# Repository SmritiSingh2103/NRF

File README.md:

# NRF
nRF24L01 is a single chip radio transceiver for the world wide 2.4 - 2.5 GHz ISM
band.

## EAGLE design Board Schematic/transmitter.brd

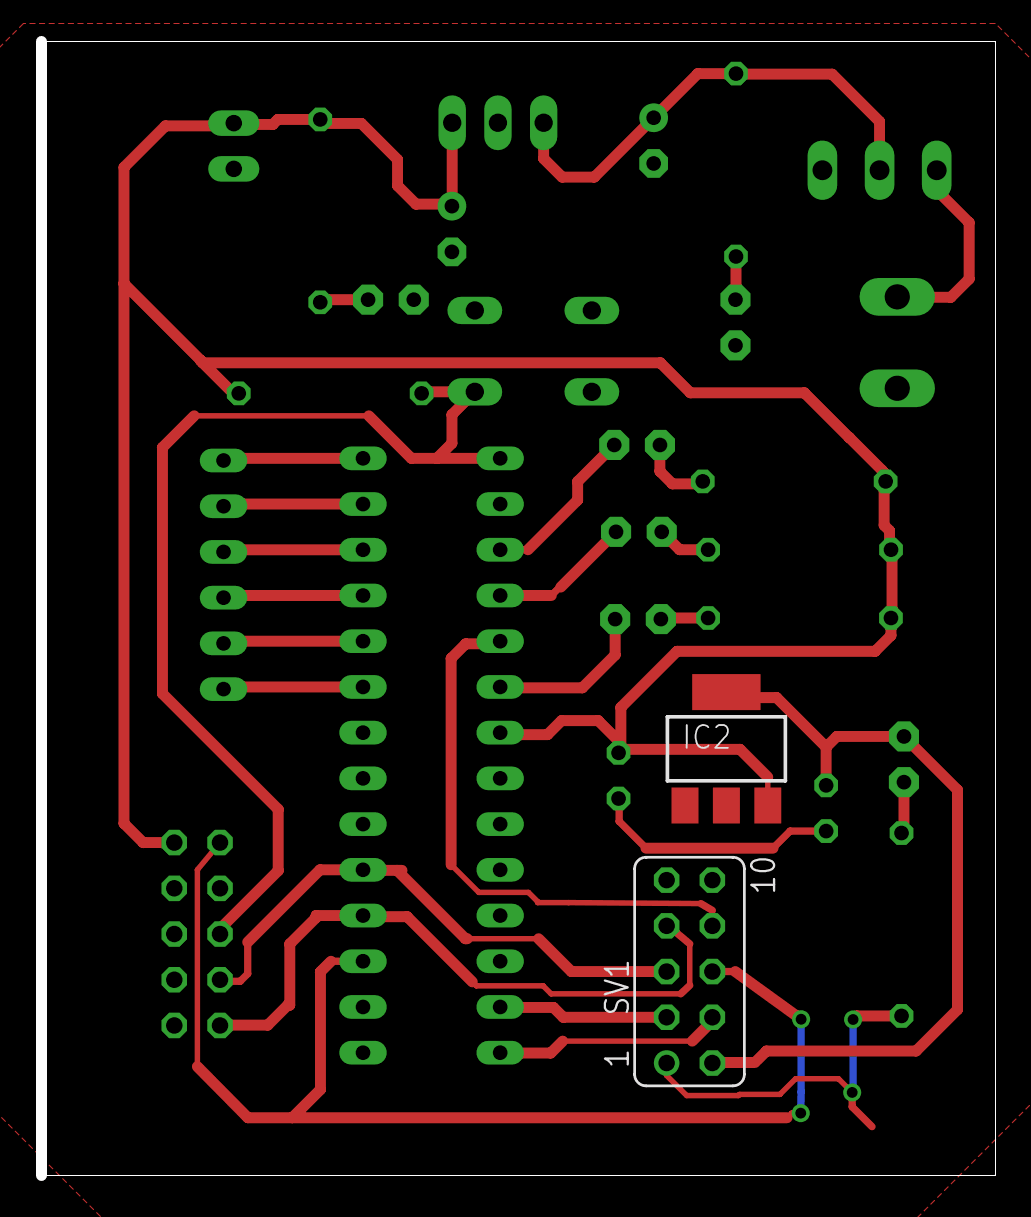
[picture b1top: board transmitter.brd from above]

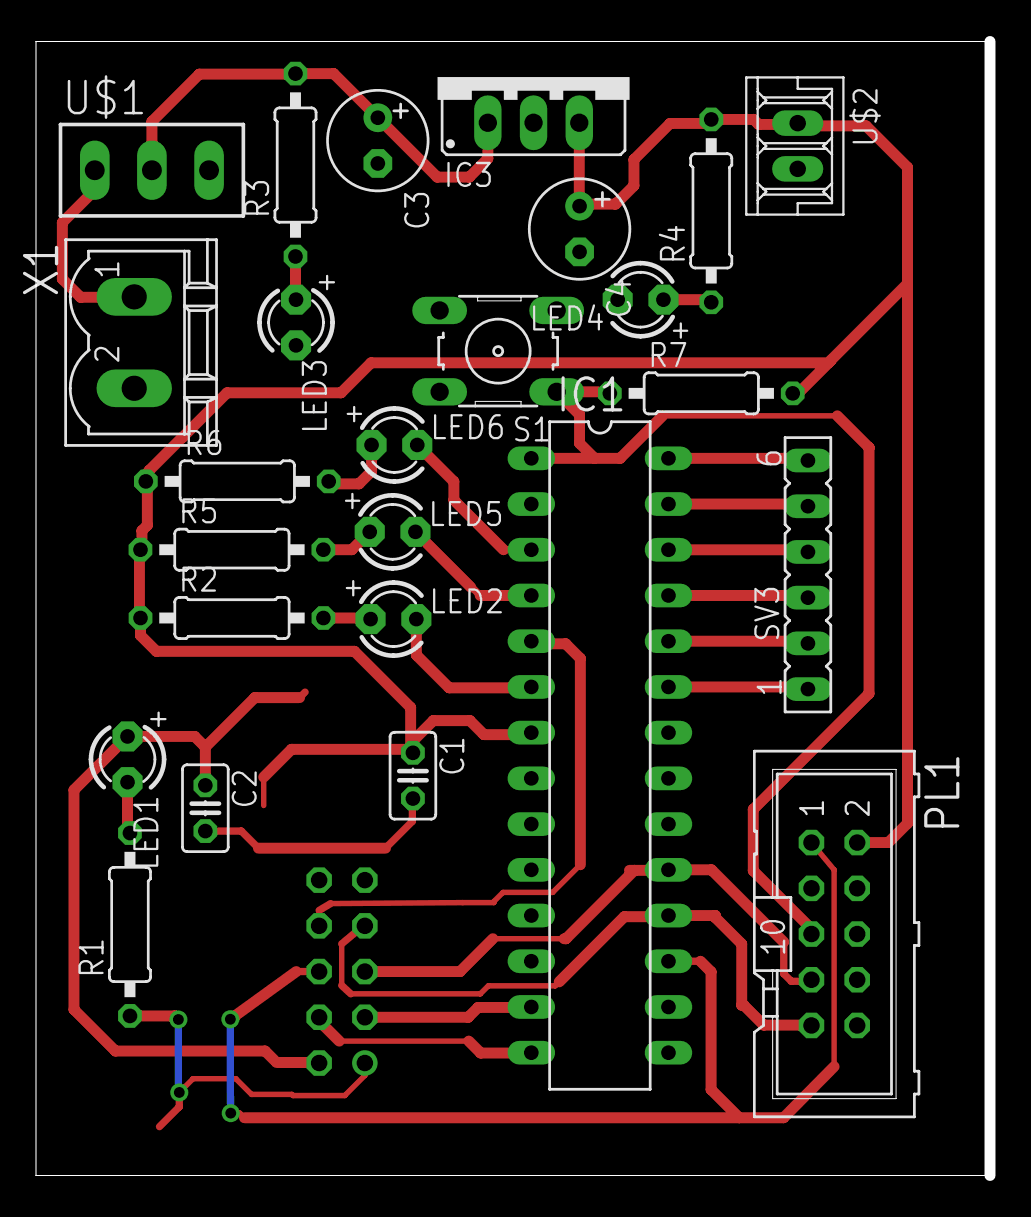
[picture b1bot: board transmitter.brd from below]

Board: 2 copper layers, 52.7 x 63.0 mm, 27 parts (25 on the bottom side), 27 nets.

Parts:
C1, C2: C025-025X050
C3, C4: E2,5-6
IC1: MEGA8-P; DIL28-3
IC2: LD117AS12TR; SOT223
IC3: 78XXS
LED1, LED2, LED3, LED4, LED5, LED6: LED3MM
PL1: ML10
R1, R2, R3, R4, R5, R6, R7: 0207/10
S1: B3F-10XX
SV1: FE05-2
SV3: FE06
U$1: SLIDE_SWITCH; SPDT
U$2: 2PIN
X1: MSTBV2

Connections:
CE: IC1.13, SV1.3
GND: C1.2, C2.2, C3.-, C4.-, IC1.8, IC1.22, IC2.1, IC3.GND, LED3.K, LED4.K, PL1.4, PL1.6, R1.1, S1.3, SV1.1, U$1.3, U$2.2, X1.2
IRQ: IC1.5, SV1.8
MISO: IC1.18, PL1.9, SV1.7
MOSI: IC1.17, PL1.1, SV1.6
unnamed: IC1.23, SV3.1
unnamed: LED5.A, R5.2
unnamed: LED6.A, R6.2
unnamed: IC1.24, SV3.2
unnamed: IC1.25, SV3.3
unnamed: IC1.26, SV3.4
unnamed: IC1.27, SV3.5
unnamed: IC1.28, SV3.6
unnamed: LED1.K, R1.2
unnamed: LED2.A, R2.2
unnamed: C3.+, IC3.IN, R3.2, U$1.2
unnamed: U$1.1, X1.1
unnamed: IC1.14, SV1.4
unnamed: LED3.A, R3.1
unnamed: IC1.6, LED2.K
unnamed: LED4.A, R4.1
unnamed: IC1.4, LED5.K
unnamed: IC1.3, LED6.K
RST: IC1.1, PL1.5, R7.1, S1.1
SCK: IC1.19, PL1.7, SV1.5
VCC: C1.1, C4.+, IC1.7, IC2.3, IC3.OUT, PL1.2, R2.1, R4.2, R7.2, U$2.1
VCC3.3: C2.1, IC2.4, LED1.A, SV1.2

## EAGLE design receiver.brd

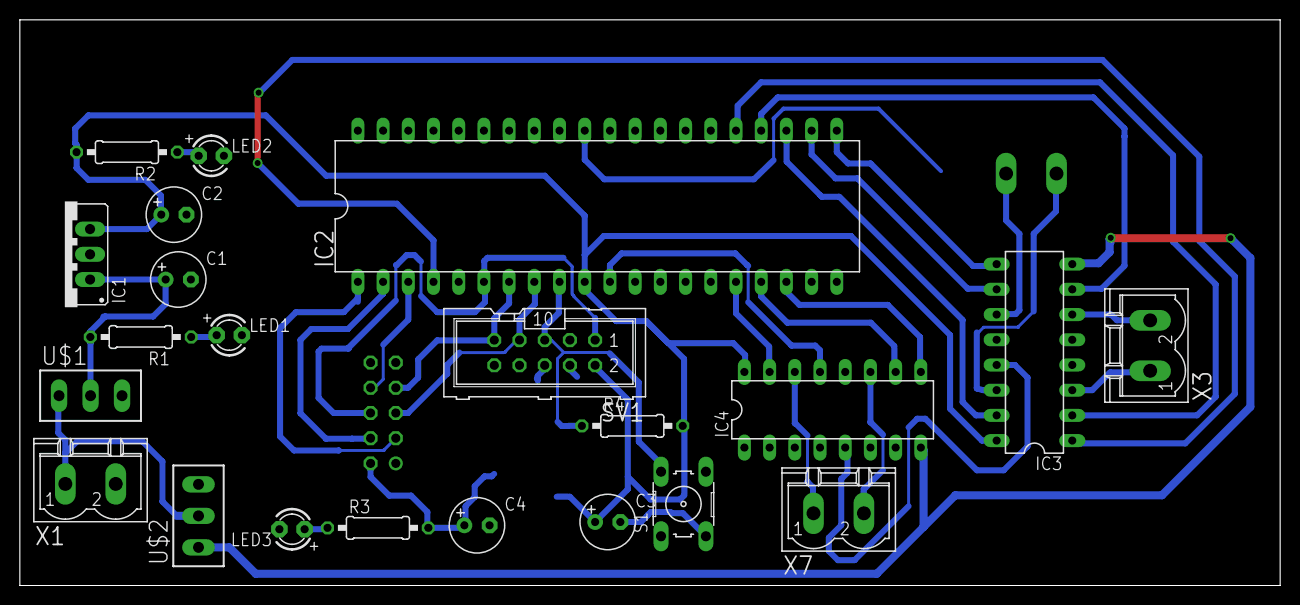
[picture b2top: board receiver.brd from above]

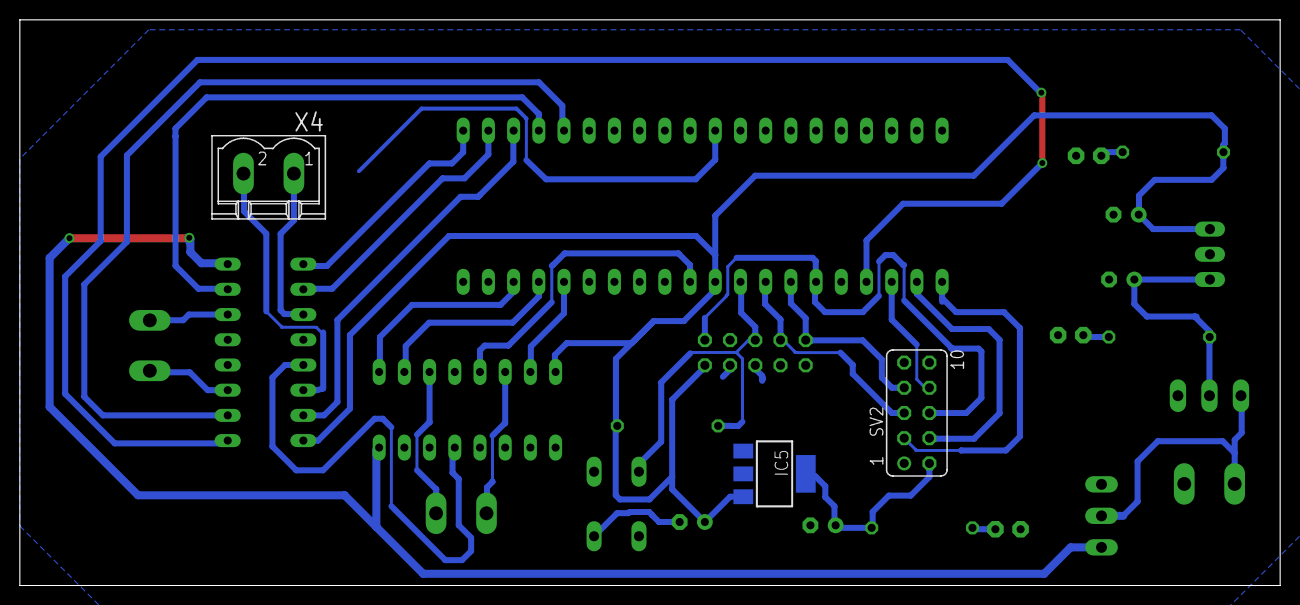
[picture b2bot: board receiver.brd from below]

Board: 2 copper layers, 127.0 x 57.0 mm, 25 parts (3 on the bottom side), 31 nets.

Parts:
C1, C2, C3, C4: E2,5-6
IC1: 78XXS
IC2: MEGA16-P; DIL40
IC3, IC4: L293D; DIL16
IC5: LD117AS25TR; SOT223
LED1, LED2, LED3: LED3MM
R1, R2, R3, R4: 0207/10
S1: B3F-10XX
SV1: ML10
SV2: FE05-2
U$1, U$2: SLIDE_SWITCH; SPDT
X1, X3, X4, X7: MSTBV2

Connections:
16: IC2.16, IC4.15
17: IC2.17, IC4.10
23: IC2.23, IC3.15
CE: IC2.1, SV2.3
CSN: IC2.2, SV2.4
EN12: IC2.4, IC3.1
EN34: IC2.21, IC3.9
GND: C1.-, C2.-, C3.-, C4.-, IC1.GND, IC2.11, IC2.31, IC3.4, IC3.5, IC3.12, IC3.13, IC4.4, IC4.5, IC4.12, IC4.13, IC5.1, LED1.K, LED2.K, LED3.K, S1.3, SV1.4, SV1.6, SV2.1, U$1.3, X1.2
IRQ: IC2.3, SV2.8
MISO: IC2.7, SV1.9, SV2.7
MOSI: IC2.6, SV1.1, SV2.6
unnamed: U$1.1, U$2.2, X1.1
unnamed: C1.+, IC1.IN, R1.2, U$1.2
unnamed: LED1.A, R1.1
unnamed: IC4.14, X7.1
unnamed: LED2.A, R2.1
unnamed: IC2.25, IC3.2
unnamed: IC4.11, X7.2
unnamed: IC2.24, IC3.7
unnamed: IC3.14, X4.2
unnamed: IC2.22, IC3.10
unnamed: IC3.11, X4.1
unnamed: IC3.3, X3.1
unnamed: IC3.6, X3.2
unnamed: LED3.A, R3.1
OC1B: IC2.18, IC4.9
RST: IC2.9, R4.1, S1.2, SV1.5
SCK: IC2.8, SV1.7, SV2.5
VCC: C2.+, C3.+, IC1.OUT, IC2.10, IC3.16, IC4.16, IC5.3, R2.2, R4.2, SV1.2
VCC3.3: C4.+, IC5.4, R3.2, SV2.2
VCC12: IC3.8, IC4.8, U$2.1

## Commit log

2017-07-08 Add files via upload
    Data sheet of the nRF24L01 module
2017-07-08 Add files via upload
    Transmitter and Receiver board designs
2017-07-08 Create \Transmitter
2017-07-08 Update \Transmitter
2017-07-08 Rename IncFile1.h to Transmitter/IncFile1.h
2017-07-08 Rename Init.h to Transmitter/Init.h
2017-07-08 Update and rename Makefile to Transmitter/Makefile
2017-07-08 Rename SPI- ATmega16 to Atmega16(Trans).atsln to Transmitter/SPI- ATmega16 to Atmega16(Trans).atsln
2017-07-08 Rename SPI- ATmega16 to Atmega16(Trans).cproj to Transmitter/SPI- ATmega16 to Atmega16(Trans).cproj
2017-07-08 Rename SPI- ATmega16 to Atmega16(Trans).componentinfo.xml to Transmitter/SPI- ATmega16 to Atmega16(Trans).componentinfo.xml
2017-07-08 Rename SPI- ATmega16 to Atmega16(Trans).eep to Transmitter/SPI- ATmega16 to Atmega16(Trans).eep
2017-07-08 Rename SPI- ATmega16 to Atmega16(Trans).hex to Transmitter/SPI- ATmega16 to Atmega16(Trans).hex
2017-07-08 Rename receiver.b## to Board Schematic/receiver.b##
2017-07-08 Rename receiver.brd to Board Schematic/receiver.brd
2017-07-08 Rename transmitter.brd to Board Schematic/transmitter.brd
2017-07-08 Rename transmitter.sch to Board Schematic/transmitter.sch
2017-07-08 Rename transmitter.b#1 to Board Schematic/transmitter.b#1
2017-07-08 Rename receiver.sch to Board Schematic/receiver.sch
2017-07-08 Rename SPI- ATmega16 to Atmega16(Trans).srec to Transmitter/SPI- ATmega16 to Atmega16(Trans).srec
2017-07-08 Rename SPI- ATmega16 to Atmega16(Trans).map to Transmitter/SPI- ATmega16 to Atmega16(Trans).map
2017-07-08 Rename SPI- ATmega16 to Atmega16(Trans).lss to Transmitter/SPI- ATmega16 to Atmega16(Trans).lss
2017-07-08 Rename SPI- ATmega16 to Atmega16.componentinfo.xml to Transmitter/SPI- ATmega16 to Atmega16.componentinfo.xml
2017-07-08 Rename lcd.h to Transmitter/lcd.h
2017-07-08 Rename main.c to Transmitter/main.c
2017-07-08 Rename main.d to Transmitter/main.d
2017-07-10 Rename SPI-ATmega to ATmega(Reciv).eep to Reciever/SPI-ATmega to ATmega(Reciv).eep
2017-07-10 Rename SPI-ATmega to ATmega(Reciv).srec to Reciever/SPI-ATmega to ATmega(Reciv).srec
2017-07-10 Rename SPI-ATmega to ATmega(Reciv).map to Reciever/SPI-ATmega to ATmega(Reciv).map
2017-07-10 Rename SPI-ATmega to ATmega(Reciv).lss to Reciever/SPI-ATmega to ATmega(Reciv).lss
2017-07-10 Rename SPI-ATmega to ATmega(Reciv).hex to Reciever/SPI-ATmega to ATmega(Reciv).hex
2017-07-10 Rename main.c to Reciever/main.c
2017-07-10 Rename main.d to Reciever/main.d
2017-07-10 Rename lcd.h to Reciever/lcd.h
2017-07-10 Rename SPI-ATmega to ATmega(Reciv).cproj to Reciever/SPI-ATmega to ATmega(Reciv).cproj
2017-07-10 Rename SPI-ATmega to ATmega(Reciv).componentinfo.xml to Reciever/SPI-ATmega to ATmega(Reciv).componentinfo.xml
2017-07-10 Rename SPI-ATmega to ATmega(Reciv).atsln to Reciever/SPI-ATmega to ATmega(Reciv).atsln
2017-07-10 Rename Init.h to Reciever/Init.h
2017-07-10 Update and rename Makefile to Reciever/Makefile
2017-07-10 Rename GccApplication21.atsln to Reciever/GccApplication21.atsln
